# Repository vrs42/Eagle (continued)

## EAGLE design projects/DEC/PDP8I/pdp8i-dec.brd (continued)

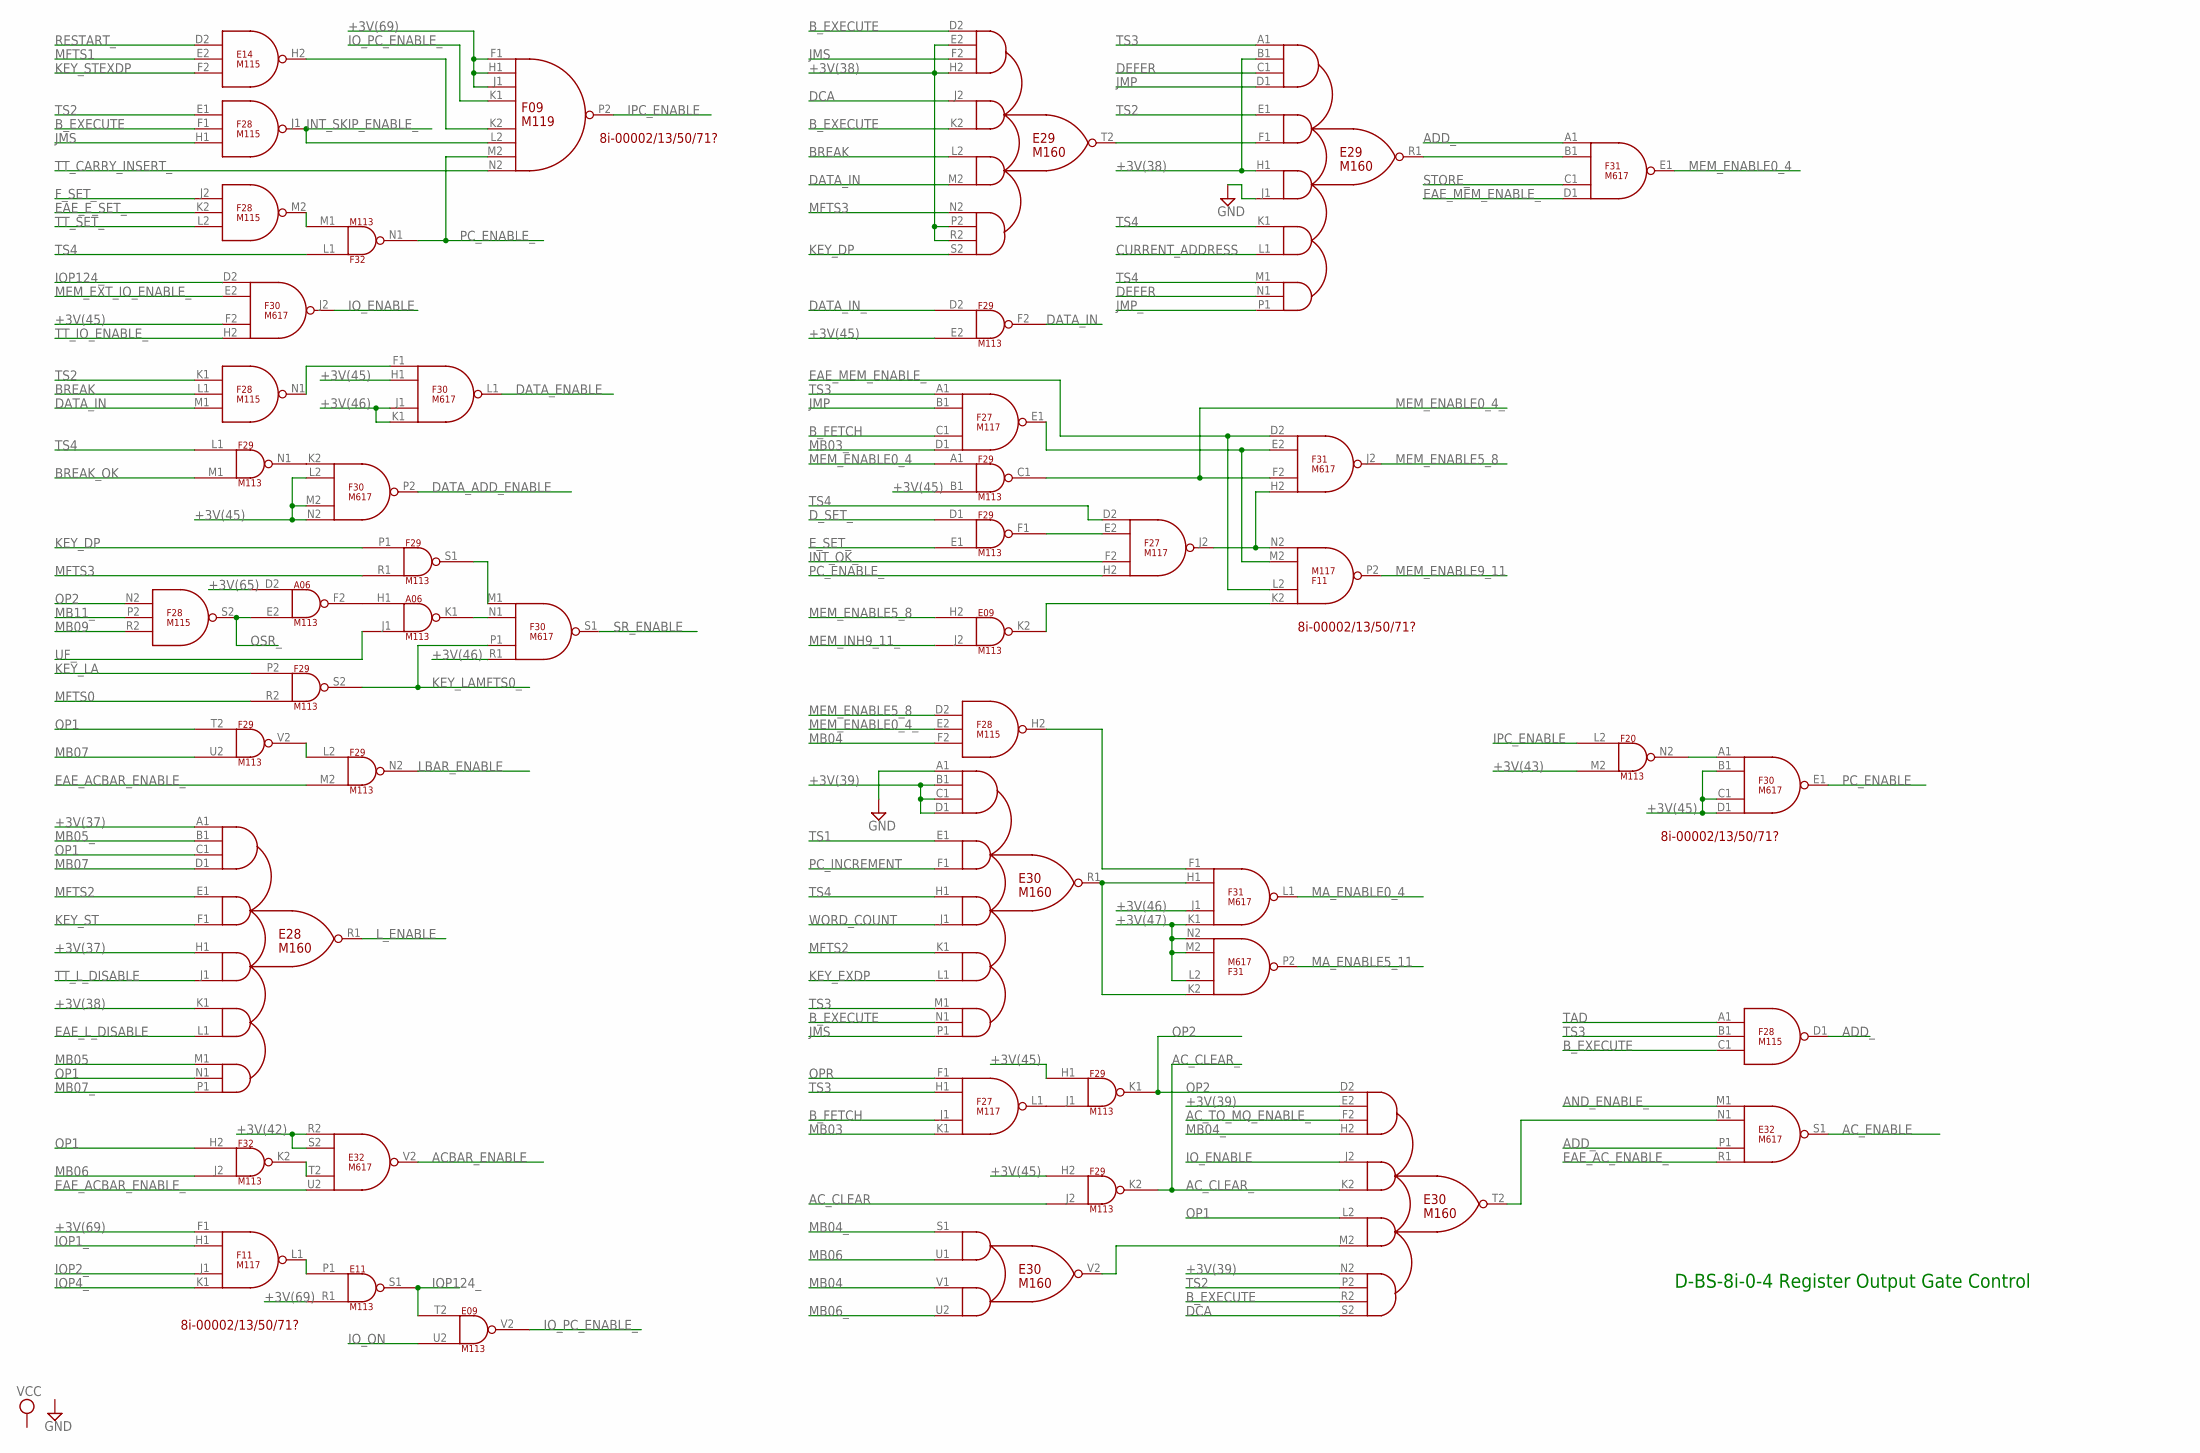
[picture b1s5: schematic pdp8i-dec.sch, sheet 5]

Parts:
A06: M113; H807
E09, E11: M113; H807
E14: M115; H807
E28, E29, E30: M160; H807
E32: M617; H807
F09: M119; H807
F11, F27: M117; H807
F20, F29, F32: M113; H807
F28: M115; H807
F30, F31: M617; H807

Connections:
+3V(37): E28.A1 (IN1A), E28.H1 (IN3A); also elsewhere on the board
+3V(38): E28.K1 (IN4A), E29.B1 (IN1B), E29.E2 (IN1B), E29.H1 (IN3A), E29.H2 (IN1D), E29.P2 (IN4B), E29.R2 (IN4C); also elsewhere on the board
+3V(39): E30.B1 (IN1B), E30.C1 (IN1C), E30.D1 (IN1D), E30.E2 (IN1B), E30.N2 (IN4A); also elsewhere on the board
+3V(42): E32.R2 (IN1), E32.S2 (IN2); also elsewhere on the board
+3V(43): F20.M2 (IN2); also elsewhere on the board
+3V(45): F29.B1 (IN2), F29.E2 (IN2), F29.H1 (IN1), F29.H2 (IN1), F30.B1 (IN2), F30.C1 (IN3), F30.D1 (IN4), F30.F2 (IN3), F30.H1 (IN2), F30.L2 (IN2), F30.M2 (IN3), F30.N2 (IN4); also elsewhere on the board
+3V(46): F30.J1 (IN3), F30.K1 (IN4), F30.R1 (IN4), F31.J1 (IN3); also elsewhere on the board
+3V(47): F31.K1 (IN4), F31.L2 (IN2), F31.M2 (IN3), F31.N2 (IN4); also elsewhere on the board
+3V(65): A06.D2 (IN1); also elsewhere on the board
+3V(69): E11.R1 (IN2), F09.F1 (IN1), F09.H1 (IN2), F09.J1 (IN3), F11.F1 (IN1); also elsewhere on the board
ACBAR_ENABLE: E32.V2 (OUT); also elsewhere on the board
AC_CLEAR: F29.J2 (IN2); also elsewhere on the board
AC_CLEAR_: E30.K2 (IN2B), F29.K2 (OUT)
AC_ENABLE: E32.S1 (OUT); also elsewhere on the board
AC_TO_MQ_ENABLE_: E30.F2 (IN1C); also elsewhere on the board
ADD_: E32.P1 (IN3), F28.D1 (OUT), F31.A1 (IN1)
AND_ENABLE_: E32.M1 (IN1); also elsewhere on the board
BREAK: E29.L2 (IN3A), F28.L1 (IN2); also elsewhere on the board
BREAK_OK: F29.M1 (IN2); also elsewhere on the board
B_EXECUTE: E29.D2 (IN1A), E29.K2 (IN2B), E30.N1 (IN5B), E30.R2 (IN4C), F28.C1 (IN3), F28.F1 (IN2); also elsewhere on the board
B_FETCH: F27.C1 (IN3), F27.J1 (IN3); also elsewhere on the board
CURRENT_ADDRESS: E29.L1 (IN4B); also elsewhere on the board
DATA_ADD_ENABLE: F30.P2 (OUT); also elsewhere on the board
DATA_ENABLE: F30.L1 (OUT); also elsewhere on the board
DATA_IN: E29.M2 (IN3B), F28.M1 (IN3), F29.F2 (OUT)
DATA_IN_: F29.D2 (IN1); also elsewhere on the board
DCA: E29.J2 (IN2A), E30.S2 (IN4D); also elsewhere on the board
DEFER: E29.C1 (IN1C), E29.N1 (IN5B); also elsewhere on the board
D_SET_: F29.D1 (IN1); also elsewhere on the board
EAE_ACBAR_ENABLE_: E32.U2 (IN4), F29.M2 (IN2); also elsewhere on the board
EAE_AC_ENABLE_: E32.R1 (IN4); also elsewhere on the board
EAE_E_SET_: F28.K2 (IN2); also elsewhere on the board
EAE_L_DISABLE: E28.L1 (IN4B); also elsewhere on the board
EAE_MEM_ENABLE_: F11.L2 (IN2), F31.D1 (IN4), F31.D2 (IN1); also elsewhere on the board
E_SET_: F29.E1 (IN2); also elsewhere on the board
F_SET_: F28.J2 (IN1); also elsewhere on the board
GND: A06.C2 (GND), A06.T1 (GND), E09.C2 (GND), E09.T1 (GND), E11.C2 (GND), E11.T1 (GND), E14.C2 (GND), E14.T1 (GND), E28.C2 (GND), E28.T1 (GND), E29.C2 (GND), E29.J1 (IN3B), E29.T1 (GND), E30.A1 (IN1A), E30.C2 (GND), E30.T1 (GND), E32.C2 (GND), E32.T1 (GND), F09.C2 (GND), F09.T1 (GND), F11.C2 (GND), F11.T1 (GND), F20.C2 (GND), F20.T1 (GND), F27.C2 (GND), F27.T1 (GND), F28.C2 (GND), F28.T1 (GND), F29.C2 (GND), F29.T1 (GND), F30.C2 (GND), F30.T1 (GND), F31.C2 (GND), F31.T1 (GND), F32.C2 (GND), F32.T1 (GND); also elsewhere on the board
INT_OK_: F27.F2 (IN3); also elsewhere on the board
INT_SKIP_ENABLE_: F09.L2 (IN6), F28.J1 (OUT); also elsewhere on the board
IOP1_: F11.H1 (IN2); also elsewhere on the board
IOP2_: F11.J1 (IN3); also elsewhere on the board
IOP4_: F11.K1 (IN4); also elsewhere on the board
IOP124_: E09.T2 (IN1), E11.S1 (OUT), F30.D2 (IN1)
IO_ENABLE: E30.J2 (IN2A), F30.J2 (OUT); also elsewhere on the board
IO_ON: E09.U2 (IN2); also elsewhere on the board
IO_PC_ENABLE_: E09.V2 (OUT), F09.K1 (IN4); also elsewhere on the board
IPC_ENABLE: F09.P2 (OUT), F20.L2 (IN1)
JMP: E29.D1 (IN1D), F27.B1 (IN2); also elsewhere on the board
JMP_: E29.P1 (IN5C); also elsewhere on the board
JMS: E29.F2 (IN1C), E30.P1 (IN5C), F28.H1 (IN3); also elsewhere on the board
KEY_DP: E29.S2 (IN4D), F29.P1 (IN1); also elsewhere on the board
KEY_EXDP: E30.L1 (IN4B); also elsewhere on the board
KEY_LA: F29.P2 (IN1); also elsewhere on the board
KEY_LAMFTS0_: F29.S2 (OUT), F30.P1 (IN3); also elsewhere on the board
KEY_ST: E28.F1 (IN2B); also elsewhere on the board
KEY_STEXDP: E14.F2 (IN3); also elsewhere on the board
LBAR_ENABLE: F29.N2 (OUT); also elsewhere on the board
L_ENABLE: E28.R1 (OUT); also elsewhere on the board
MA_ENABLE0_4: F31.L1 (OUT); also elsewhere on the board
MA_ENABLE5_11: F31.P2 (OUT); also elsewhere on the board
MB03: F27.K1 (IN4); also elsewhere on the board
MB03_: F27.D1 (IN4); also elsewhere on the board
MB04: E30.V1 (IN2A), F28.F2 (IN3); also elsewhere on the board
MB04_: E30.H2 (IN1D), E30.S1 (IN1A); also elsewhere on the board
MB05: E28.M1 (IN5A); also elsewhere on the board
MB05_: E28.B1 (IN1B); also elsewhere on the board
MB06: E30.U1 (IN1B), F32.J2 (IN2); also elsewhere on the board
MB06_: E30.U2 (IN2B); also elsewhere on the board
MB07: E28.D1 (IN1D), F29.U2 (IN2); also elsewhere on the board
MB07_: E28.P1 (IN5C); also elsewhere on the board
MB09: F28.R2 (IN3); also elsewhere on the board
MB11_: F28.P2 (IN2); also elsewhere on the board
MEM_ENABLE0_4: F29.A1 (IN1), F31.E1 (OUT); also elsewhere on the board
MEM_ENABLE0_4_: F28.E2 (IN2), F29.C1 (OUT), F31.F2 (IN3)
MEM_ENABLE5_8: E09.H2 (IN1), F28.D2 (IN1), F31.J2 (OUT); also elsewhere on the board
MEM_ENABLE9_11: F11.P2 (OUT); also elsewhere on the board
MEM_EXT_IO_ENABLE_: F30.E2 (IN2); also elsewhere on the board
MEM_INH9_11_: E09.J2 (IN2); also elsewhere on the board
MFTS0: F29.R2 (IN2); also elsewhere on the board
MFTS1: E14.E2 (IN2); also elsewhere on the board
MFTS2: E28.E1 (IN2A), E30.K1 (IN4A); also elsewhere on the board
MFTS3: E29.N2 (IN4A), F29.R1 (IN2); also elsewhere on the board
unnamed: E29.R1 (OUT), F31.B1 (IN2)
unnamed: E09.K2 (OUT), F11.K2 (IN1)
unnamed: F27.E2 (IN2), F29.F1 (OUT)
unnamed: F11.M2 (IN3), F27.E1 (OUT), F31.E2 (IN2)
unnamed: E30.R1 (OUT), F31.H1 (IN2), F31.K2 (IN1)
unnamed: A06.F2 (OUT), A06.H1 (IN1)
unnamed: E14.H2 (OUT), F09.K2 (IN5)
unnamed: F28.M2 (OUT), F32.M1 (IN2)
unnamed: F29.L2 (IN1), F29.V2 (OUT)
unnamed: F28.N1 (OUT), F30.F1 (IN1)
unnamed: E29.F1 (IN2B), E29.T2 (OUT)
unnamed: F29.N1 (OUT), F30.K2 (IN1)
unnamed: A06.K1 (OUT), F30.N1 (IN2)
unnamed: F29.S1 (OUT), F30.M1 (IN1)
unnamed: E32.T2 (IN3), F32.K2 (OUT)
unnamed: F11.N2 (IN4), F27.J2 (OUT), F31.H2 (IN4)
unnamed: F28.H2 (OUT), F31.F1 (IN1)
unnamed: F27.L1 (OUT), F29.J1 (IN2)
unnamed: E30.T2 (OUT), E32.N1 (IN2)
unnamed: E30.M2 (IN3B), E30.V2 (OUT)
unnamed: E11.P1 (IN1), F11.L1 (OUT)
unnamed: F20.N2 (OUT), F30.A1 (IN1)
OP1: E28.C1 (IN1C), E28.N1 (IN5B), E30.L2 (IN3A), F29.T2 (IN1), F32.H2 (IN1); also elsewhere on the board
OP2: E30.D2 (IN1A), F28.N2 (IN1), F29.K1 (OUT); also elsewhere on the board
OPR: F27.F1 (IN1); also elsewhere on the board
OSR_: A06.E2 (IN2), F28.S2 (OUT)
PC_ENABLE: F30.E1 (OUT); also elsewhere on the board
PC_ENABLE_: F09.M2 (IN7), F27.H2 (IN4), F32.N1 (OUT); also elsewhere on the board
PC_INCREMENT: E30.F1 (IN2B); also elsewhere on the board
RESTART_: E14.D2 (IN1); also elsewhere on the board
SR_ENABLE: F30.S1 (OUT); also elsewhere on the board
STORE_: F31.C1 (IN3); also elsewhere on the board
TAD: F28.A1 (IN1); also elsewhere on the board
TS1: E30.E1 (IN2A); also elsewhere on the board
TS2: E29.E1 (IN2A), E30.P2 (IN4B), F28.E1 (IN1), F28.K1 (IN1); also elsewhere on the board
TS3: E29.A1 (IN1A), E30.M1 (IN5A), F27.A1 (IN1), F27.H1 (IN2), F28.B1 (IN2); also elsewhere on the board
TS4: E29.K1 (IN4A), E29.M1 (IN5A), E30.H1 (IN3A), F27.D2 (IN1), F29.L1 (IN1), F32.L1 (IN1); also elsewhere on the board
TT_CARRY_INSERT_: F09.N2 (IN8); also elsewhere on the board
TT_IO_ENABLE_: F30.H2 (IN4); also elsewhere on the board
TT_L_DISABLE: E28.J1 (IN3B); also elsewhere on the board
TT_SET_: F28.L2 (IN3); also elsewhere on the board
UF_: A06.J1 (IN2); also elsewhere on the board
VCC: A06.A2 (VCC), E09.A2 (VCC), E11.A2 (VCC), E14.A2 (VCC), E28.A2 (VCC), E29.A2 (VCC), E30.A2 (VCC), E32.A2 (VCC), F09.A2 (VCC), F11.A2 (VCC), F20.A2 (VCC), F27.A2 (VCC), F28.A2 (VCC), F29.A2 (VCC), F30.A2 (VCC), F31.A2 (VCC), F32.A2 (VCC); also elsewhere on the board
WORD_COUNT: E30.J1 (IN3B); also elsewhere on the board

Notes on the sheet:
D-BS-8i-0-4 Register Output Gate Control
8i-00002/13/50/71?

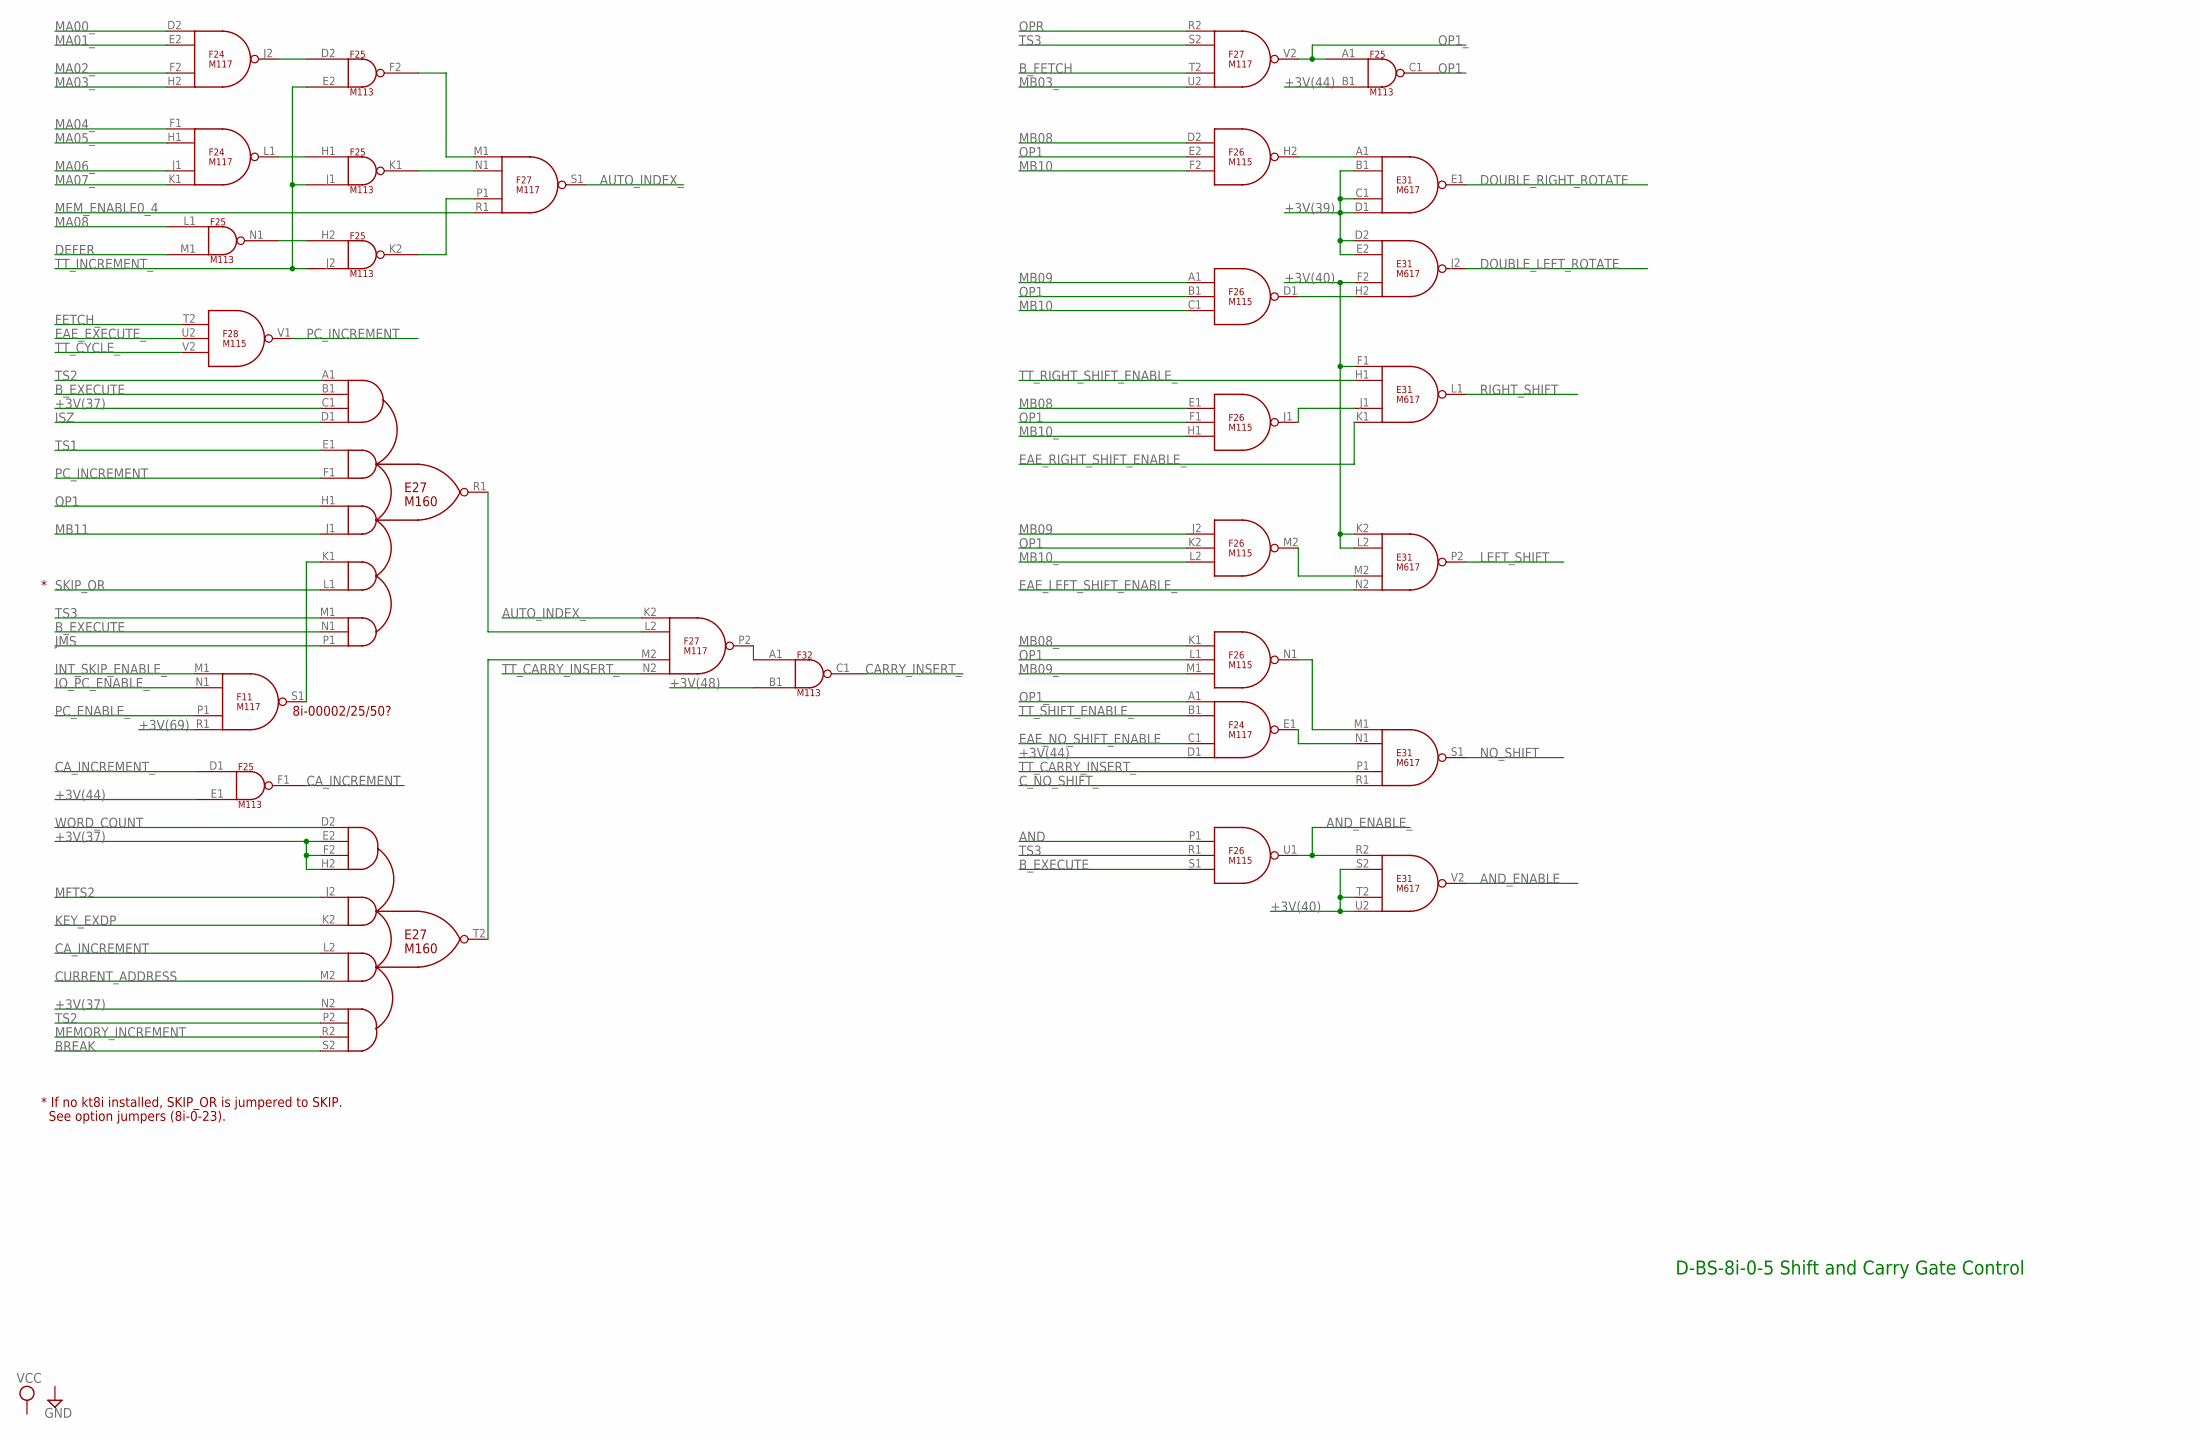
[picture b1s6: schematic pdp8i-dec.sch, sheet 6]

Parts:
E27: M160; H807
E31: M617; H807
F11, F24, F27: M117; H807
F25, F32: M113; H807
F26, F28: M115; H807

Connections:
+3V(37): E27.C1 (IN1C), E27.E2 (IN1B), E27.F2 (IN1C), E27.H2 (IN1D), E27.N2 (IN4A); also elsewhere on the board
+3V(39): E31.B1 (IN2), E31.C1 (IN3), E31.D1 (IN4), E31.D2 (IN1), E31.E2 (IN2); also elsewhere on the board
+3V(40): E31.F1 (IN1), E31.F2 (IN3), E31.K2 (IN1), E31.L2 (IN2), E31.S2 (IN2), E31.T2 (IN3), E31.U2 (IN4); also elsewhere on the board
+3V(44): F24.D1 (IN4), F25.B1 (IN2), F25.E1 (IN2); also elsewhere on the board
+3V(48): F32.B1 (IN2); also elsewhere on the board
+3V(69): F11.R1 (IN4); also elsewhere on the board
AND: F26.P1 (IN1); also elsewhere on the board
AND_ENABLE: E31.V2 (OUT); also elsewhere on the board
AND_ENABLE_: E31.R2 (IN1), F26.U1 (OUT); also elsewhere on the board
AUTO_INDEX_: F27.K2 (IN1), F27.S1 (OUT)
BREAK: E27.S2 (IN4D); also elsewhere on the board
B_EXECUTE: E27.B1 (IN1B), E27.N1 (IN5B), F26.S1 (IN3); also elsewhere on the board
B_FETCH: F27.T2 (IN3); also elsewhere on the board
CARRY_INSERT_: F32.C1 (OUT); also elsewhere on the board
CA_INCREMENT: E27.L2 (IN3A), F25.F1 (OUT)
CA_INCREMENT_: F25.D1 (IN1); also elsewhere on the board
CURRENT_ADDRESS: E27.M2 (IN3B); also elsewhere on the board
C_NO_SHIFT_: E31.R1 (IN4); also elsewhere on the board
DEFER: F25.M1 (IN2); also elsewhere on the board
DOUBLE_LEFT_ROTATE: E31.J2 (OUT); also elsewhere on the board
DOUBLE_RIGHT_ROTATE: E31.E1 (OUT); also elsewhere on the board
EAE_EXECUTE_: F28.U2 (IN2); also elsewhere on the board
EAE_LEFT_SHIFT_ENABLE_: E31.N2 (IN4); also elsewhere on the board
EAE_NO_SHIFT_ENABLE: F24.C1 (IN3); also elsewhere on the board
EAE_RIGHT_SHIFT_ENABLE_: E31.K1 (IN4); also elsewhere on the board
FETCH_: F28.T2 (IN1); also elsewhere on the board
GND: E27.C2 (GND), E27.T1 (GND), E31.C2 (GND), E31.T1 (GND), F11.C2 (GND), F11.T1 (GND), F24.C2 (GND), F24.T1 (GND), F25.C2 (GND), F25.T1 (GND), F26.C2 (GND), F26.T1 (GND), F27.C2 (GND), F27.T1 (GND), F28.C2 (GND), F28.T1 (GND), F32.C2 (GND), F32.T1 (GND); also elsewhere on the board
INT_SKIP_ENABLE_: F11.M1 (IN1); also elsewhere on the board
IO_PC_ENABLE_: F11.N1 (IN2); also elsewhere on the board
ISZ: E27.D1 (IN1D); also elsewhere on the board
JMS: E27.P1 (IN5C); also elsewhere on the board
KEY_EXDP: E27.K2 (IN2B); also elsewhere on the board
LEFT_SHIFT: E31.P2 (OUT); also elsewhere on the board
MA00_: F24.D2 (IN1); also elsewhere on the board
MA01_: F24.E2 (IN2); also elsewhere on the board
MA02_: F24.F2 (IN3); also elsewhere on the board
MA03_: F24.H2 (IN4); also elsewhere on the board
MA04_: F24.F1 (IN1); also elsewhere on the board
MA05_: F24.H1 (IN2); also elsewhere on the board
MA06_: F24.J1 (IN3); also elsewhere on the board
MA07_: F24.K1 (IN4); also elsewhere on the board
MA08: F25.L1 (IN1); also elsewhere on the board
MB03_: F27.U2 (IN4); also elsewhere on the board
MB08: F26.D2 (IN1), F26.E1 (IN1); also elsewhere on the board
MB08_: F26.K1 (IN1); also elsewhere on the board
MB09: F26.A1 (IN1), F26.J2 (IN1); also elsewhere on the board
MB09_: F26.M1 (IN3); also elsewhere on the board
MB10: F26.C1 (IN3), F26.F2 (IN3); also elsewhere on the board
MB10_: F26.H1 (IN3), F26.L2 (IN3); also elsewhere on the board
MB11: E27.J1 (IN3B); also elsewhere on the board
MEMORY_INCREMENT: E27.R2 (IN4C); also elsewhere on the board
MEM_ENABLE0_4: F27.R1 (IN4); also elsewhere on the board
MFTS2: E27.J2 (IN2A); also elsewhere on the board
unnamed: F25.H2 (IN1), F25.N1 (OUT)
unnamed: F24.L1 (OUT), F25.H1 (IN1)
unnamed: F24.J2 (OUT), F25.D2 (IN1)
unnamed: E27.K1 (IN4A), F11.S1 (OUT)
unnamed: E27.T2 (OUT), F27.M2 (IN3)
unnamed: E27.R1 (OUT), F27.L2 (IN2)
unnamed: E31.N1 (IN2), F24.E1 (OUT)
unnamed: F25.K2 (OUT), F27.P1 (IN3)
unnamed: F25.K1 (OUT), F27.N1 (IN2)
unnamed: F25.F2 (OUT), F27.M1 (IN1)
unnamed: E31.M1 (IN1), F26.N1 (OUT)
unnamed: F27.P2 (OUT), F32.A1 (IN1)
unnamed: E31.H2 (IN4), F26.D1 (OUT)
unnamed: E31.J1 (IN3), F26.J1 (OUT)
unnamed: E31.M2 (IN3), F26.M2 (OUT)
unnamed: E31.A1 (IN1), F26.H2 (OUT)
NO_SHIFT: E31.S1 (OUT); also elsewhere on the board
OP1: E27.H1 (IN3A), F25.C1 (OUT), F26.B1 (IN2), F26.E2 (IN2), F26.F1 (IN2), F26.K2 (IN2), F26.L1 (IN2); also elsewhere on the board
OP1_: F24.A1 (IN1), F25.A1 (IN1), F27.V2 (OUT)
OPR: F27.R2 (IN1); also elsewhere on the board
PC_ENABLE_: F11.P1 (IN3); also elsewhere on the board
PC_INCREMENT: E27.F1 (IN2B), F28.V1 (OUT); also elsewhere on the board
RIGHT_SHIFT: E31.L1 (OUT); also elsewhere on the board
SKIP_OR: E27.L1 (IN4B); also elsewhere on the board
TS1: E27.E1 (IN2A); also elsewhere on the board
TS2: E27.A1 (IN1A), E27.P2 (IN4B); also elsewhere on the board
TS3: E27.M1 (IN5A), F26.R1 (IN2), F27.S2 (IN2); also elsewhere on the board
TT_CARRY_INSERT_: E31.P1 (IN3), F27.N2 (IN4); also elsewhere on the board
TT_CYCLE_: F28.V2 (IN3); also elsewhere on the board
TT_INCREMENT_: F25.E2 (IN2), F25.J1 (IN2), F25.J2 (IN2); also elsewhere on the board
TT_RIGHT_SHIFT_ENABLE_: E31.H1 (IN2); also elsewhere on the board
TT_SHIFT_ENABLE_: F24.B1 (IN2); also elsewhere on the board
VCC: E27.A2 (VCC), E31.A2 (VCC), F11.A2 (VCC), F24.A2 (VCC), F25.A2 (VCC), F26.A2 (VCC), F27.A2 (VCC), F28.A2 (VCC), F32.A2 (VCC); also elsewhere on the board
WORD_COUNT: E27.D2 (IN1A); also elsewhere on the board

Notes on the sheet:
D-BS-8i-0-5 Shift and Carry Gate Control
8i-00002/25/50?
* If no kt8i installed, SKIP_OR is jumpered to SKIP.
See option jumpers (8i-0-23).

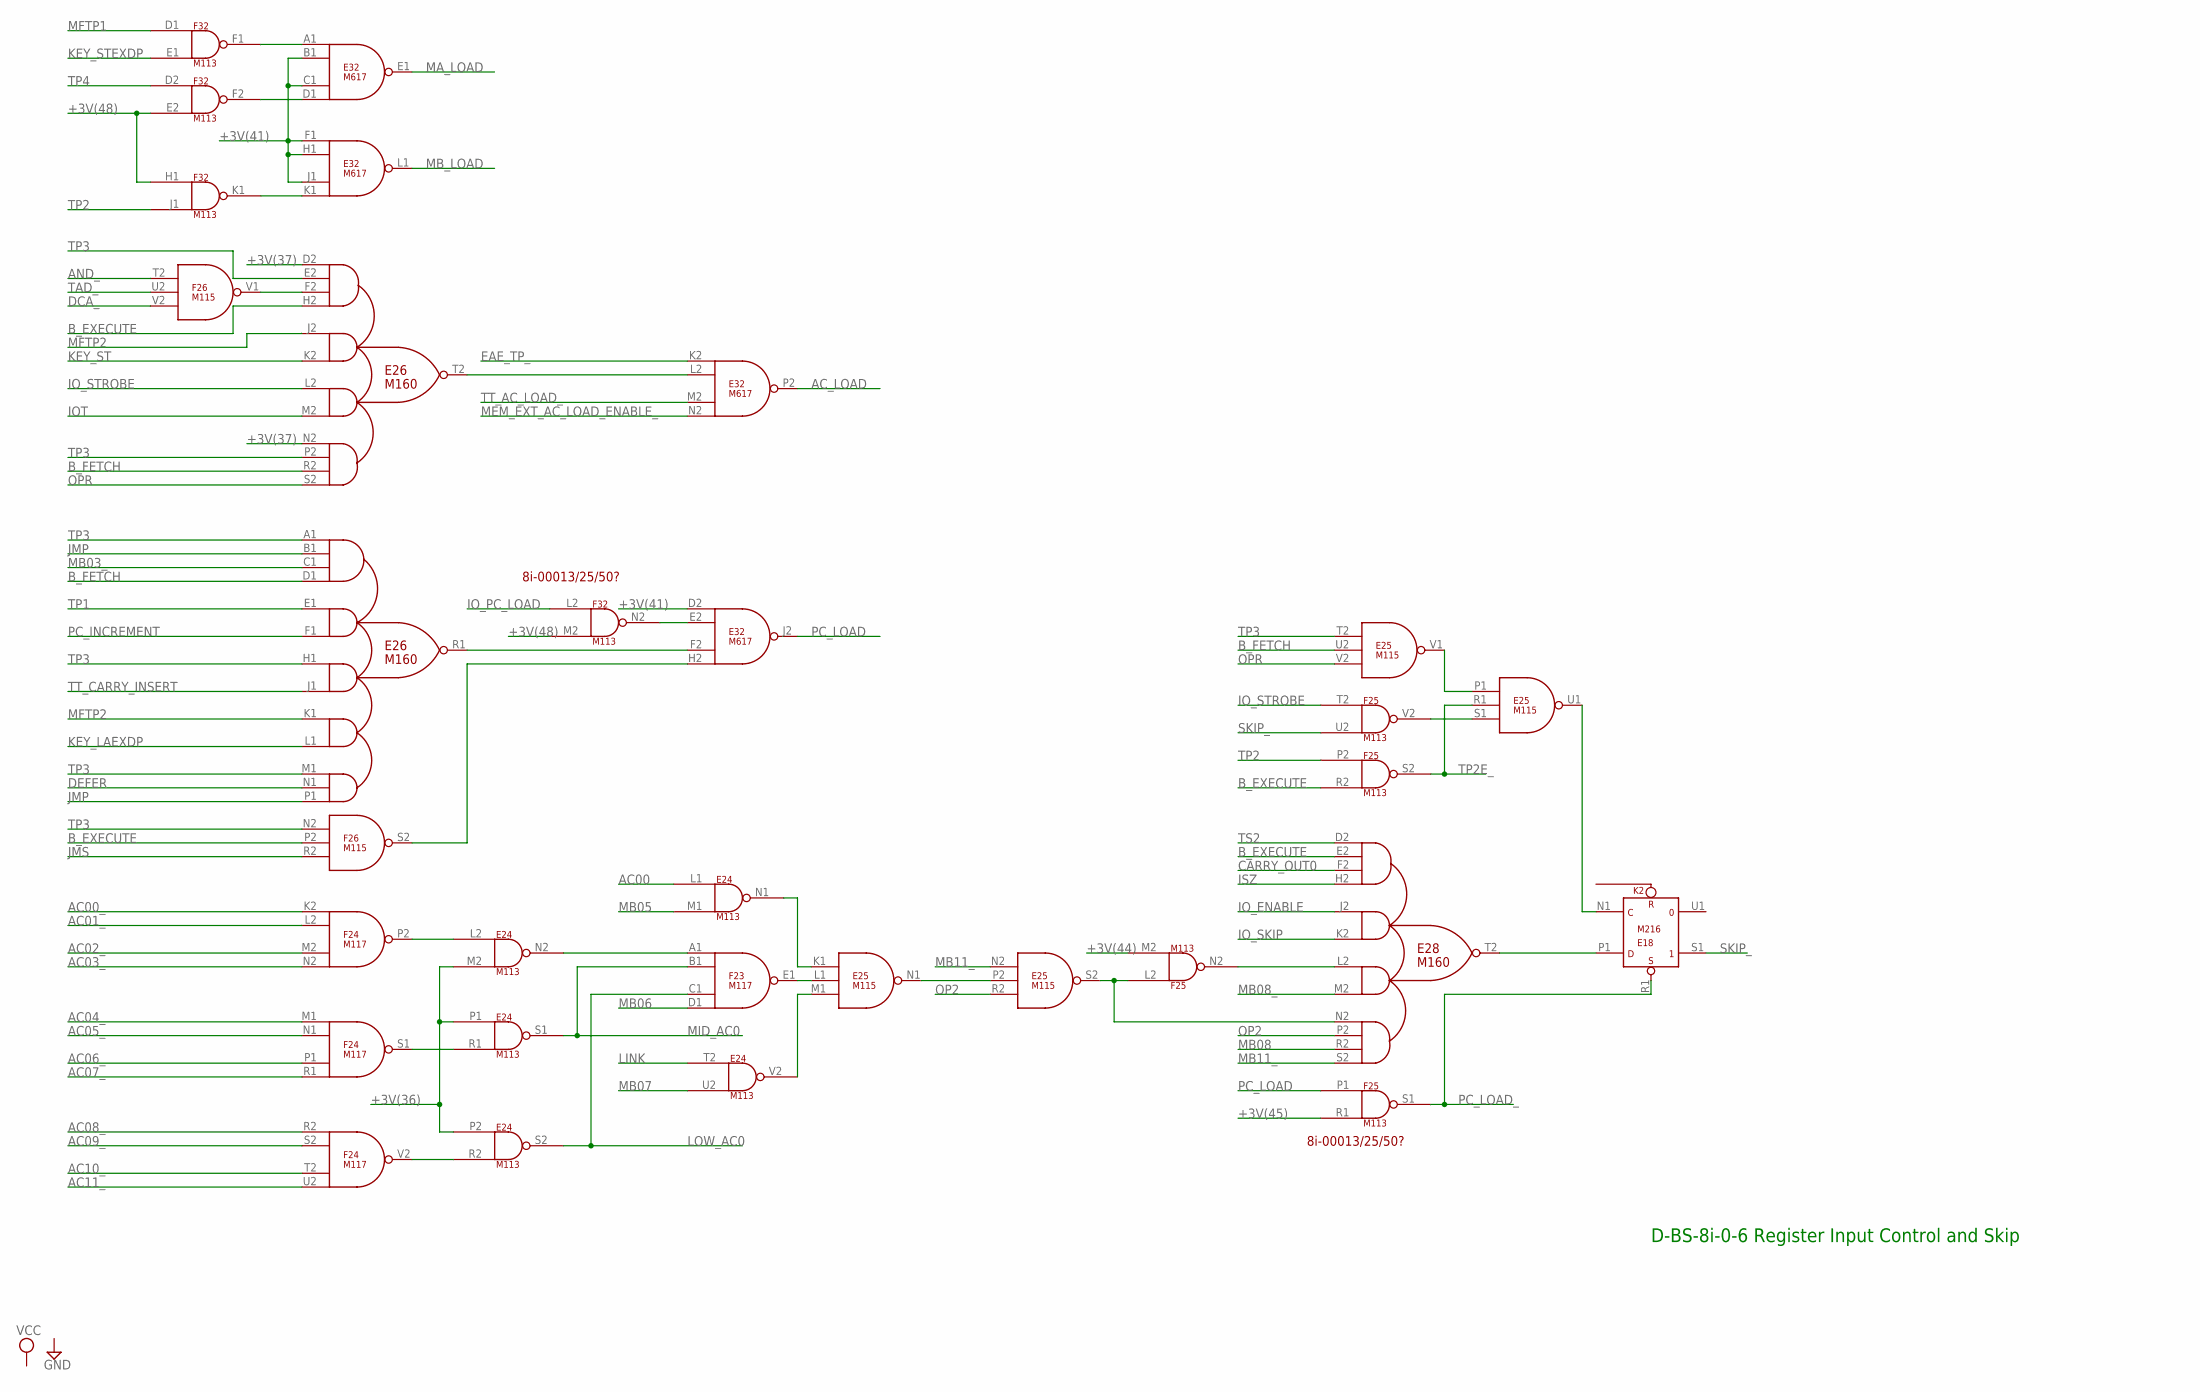
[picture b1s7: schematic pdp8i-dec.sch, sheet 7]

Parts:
E18: M216; H807
E24: M113; H807
E25: M115; H807
E26, E28: M160; H807
E32: M617; H807
F23, F24: M117; H807
F25, F32: M113; H807
F26: M115; H807

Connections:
+3V(36): E24.M2 (IN2), E24.P1 (IN1), E24.P2 (IN1); also elsewhere on the board
+3V(37): E26.D2 (IN1A), E26.N2 (IN4A); also elsewhere on the board
+3V(41): E32.B1 (IN2), E32.C1 (IN3), E32.D2 (IN1), E32.F1 (IN1), E32.H1 (IN2), E32.J1 (IN3); also elsewhere on the board
+3V(44): F25.M2 (IN2); also elsewhere on the board
+3V(45): F25.R1 (IN2); also elsewhere on the board
+3V(48): F32.E2 (IN2), F32.H1 (IN1), F32.M2 (IN2); also elsewhere on the board
AC00: E24.L1 (IN1); also elsewhere on the board
AC00_: F24.K2 (IN1); also elsewhere on the board
AC01_: F24.L2 (IN2); also elsewhere on the board
AC02_: F24.M2 (IN3); also elsewhere on the board
AC03_: F24.N2 (IN4); also elsewhere on the board
AC04_: F24.M1 (IN1); also elsewhere on the board
AC05_: F24.N1 (IN2); also elsewhere on the board
AC06_: F24.P1 (IN3); also elsewhere on the board
AC07_: F24.R1 (IN4); also elsewhere on the board
AC08_: F24.R2 (IN1); also elsewhere on the board
AC09_: F24.S2 (IN2); also elsewhere on the board
AC10_: F24.T2 (IN3); also elsewhere on the board
AC11_: F24.U2 (IN4); also elsewhere on the board
AC_LOAD: E32.P2 (OUT); also elsewhere on the board
AND_: F26.T2 (IN1); also elsewhere on the board
B_EXECUTE: E26.H2 (IN1D), E28.E2 (IN1B), F25.R2 (IN2), F26.P2 (IN2); also elsewhere on the board
B_FETCH: E25.U2 (IN2), E26.D1 (IN1D), E26.R2 (IN4C); also elsewhere on the board
CARRY_OUT0: E28.F2 (IN1C); also elsewhere on the board
DCA_: F26.V2 (IN3); also elsewhere on the board
DEFER: E26.N1 (IN5B); also elsewhere on the board
EAE_TP_: E32.K2 (IN1); also elsewhere on the board
GND: E18.C2 (GND), E18.T1 (GND), E24.C2 (GND), E24.T1 (GND), E25.C2 (GND), E25.T1 (GND), E26.C2 (GND), E26.T1 (GND), E28.C2 (GND), E28.T1 (GND), E32.C2 (GND), E32.T1 (GND), F23.C2 (GND), F23.T1 (GND), F24.C2 (GND), F24.T1 (GND), F25.C2 (GND), F25.T1 (GND), F26.C2 (GND), F26.T1 (GND), F32.C2 (GND), F32.T1 (GND); also elsewhere on the board
IOT: E26.M2 (IN3B); also elsewhere on the board
IO_ENABLE: E28.J2 (IN2A); also elsewhere on the board
IO_PC_LOAD: F32.L2 (IN1); also elsewhere on the board
IO_SKIP: E28.K2 (IN2B); also elsewhere on the board
IO_STROBE: E26.L2 (IN3A), F25.T2 (IN1); also elsewhere on the board
ISZ: E28.H2 (IN1D); also elsewhere on the board
JMP: E26.B1 (IN1B), E26.P1 (IN5C); also elsewhere on the board
JMS: F26.R2 (IN3); also elsewhere on the board
KEY_LAEXDP: E26.L1 (IN4B); also elsewhere on the board
KEY_ST: E26.K2 (IN2B); also elsewhere on the board
KEY_STEXDP: F32.E1 (IN2); also elsewhere on the board
LINK: E24.T2 (IN1); also elsewhere on the board
LOW_AC0: E24.S2 (OUT), F23.C1 (IN3); also elsewhere on the board
MA_LOAD: E32.E1 (OUT); also elsewhere on the board
MB03_: E26.C1 (IN1C); also elsewhere on the board
MB05: E24.M1 (IN2); also elsewhere on the board
MB06: F23.D1 (IN4); also elsewhere on the board
MB07: E24.U2 (IN2); also elsewhere on the board
MB08: E28.R2 (IN4C); also elsewhere on the board
MB08_: E28.M2 (IN3B); also elsewhere on the board
MB11_: E25.N2 (IN1), E28.S2 (IN4D); also elsewhere on the board
MB_LOAD: E32.L1 (OUT); also elsewhere on the board
MEM_EXT_AC_LOAD_ENABLE_: E32.N2 (IN4); also elsewhere on the board
MFTP1: F32.D1 (IN1); also elsewhere on the board
MFTP2: E26.J2 (IN2A), E26.K1 (IN4A); also elsewhere on the board
MID_AC0: E24.S1 (OUT), F23.B1 (IN2); also elsewhere on the board
unnamed: E26.F2 (IN1C), F26.V1 (OUT)
unnamed: E26.T2 (OUT), E32.L2 (IN2)
unnamed: E26.R1 (OUT), E32.F2 (IN3)
unnamed: E32.H2 (IN4), F26.S2 (OUT)
unnamed: E24.R2 (IN2), F24.V2 (OUT)
unnamed: E24.R1 (IN2), F24.S1 (OUT)
unnamed: E24.L2 (IN1), F24.P2 (OUT)
unnamed: E25.L1 (IN2), F23.E1 (OUT)
unnamed: E24.V2 (OUT), E25.M1 (IN3)
unnamed: E24.N2 (OUT), F23.A1 (IN1)
unnamed: E24.N1 (OUT), E25.K1 (IN1)
unnamed: E25.N1 (OUT), E25.P2 (IN2)
unnamed: E28.L2 (IN3A), F25.N2 (OUT)
unnamed: E25.S2 (OUT), E28.N2 (IN4A), F25.L2 (IN1)
unnamed: E18.P1 (D), E28.T2 (OUT)
unnamed: E32.D1 (IN4), F32.F2 (OUT)
unnamed: E32.A1 (IN1), F32.F1 (OUT)
unnamed: E18.N1 (C), E25.U1 (OUT)
unnamed: E32.K1 (IN4), F32.K1 (OUT)
unnamed: E25.P1 (IN1), E25.V1 (OUT)
unnamed: E25.S1 (IN3), F25.V2 (OUT)
unnamed: E32.E2 (IN2), F32.N2 (OUT)
OP2: E25.R2 (IN3), E28.P2 (IN4B); also elsewhere on the board
OPR: E25.V2 (IN3), E26.S2 (IN4D); also elsewhere on the board
PC_INCREMENT: E26.F1 (IN2B); also elsewhere on the board
PC_LOAD: E32.J2 (OUT), F25.P1 (IN1); also elsewhere on the board
PC_LOAD_: E18.R1 (S), F25.S1 (OUT); also elsewhere on the board
SKIP_: E18.S1 (1), F25.U2 (IN2); also elsewhere on the board
TAD_: F26.U2 (IN2); also elsewhere on the board
TP1: E26.E1 (IN2A); also elsewhere on the board
TP2: F25.P2 (IN1), F32.J1 (IN2); also elsewhere on the board
TP2E_: E25.R1 (IN2), F25.S2 (OUT); also elsewhere on the board
TP3: E25.T2 (IN1), E26.A1 (IN1A), E26.E2 (IN1B), E26.H1 (IN3A), E26.M1 (IN5A), E26.P2 (IN4B), F26.N2 (IN1); also elsewhere on the board
TP4: F32.D2 (IN1); also elsewhere on the board
TS2: E28.D2 (IN1A); also elsewhere on the board
TT_AC_LOAD_: E32.M2 (IN3); also elsewhere on the board
TT_CARRY_INSERT: E26.J1 (IN3B); also elsewhere on the board
VCC: E18.A2 (VCC), E24.A2 (VCC), E25.A2 (VCC), E26.A2 (VCC), E28.A2 (VCC), E32.A2 (VCC), F23.A2 (VCC), F24.A2 (VCC), F25.A2 (VCC), F26.A2 (VCC), F32.A2 (VCC); also elsewhere on the board

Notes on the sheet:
D-BS-8i-0-6 Register Input Control and Skip
8i-00013/25/50?
